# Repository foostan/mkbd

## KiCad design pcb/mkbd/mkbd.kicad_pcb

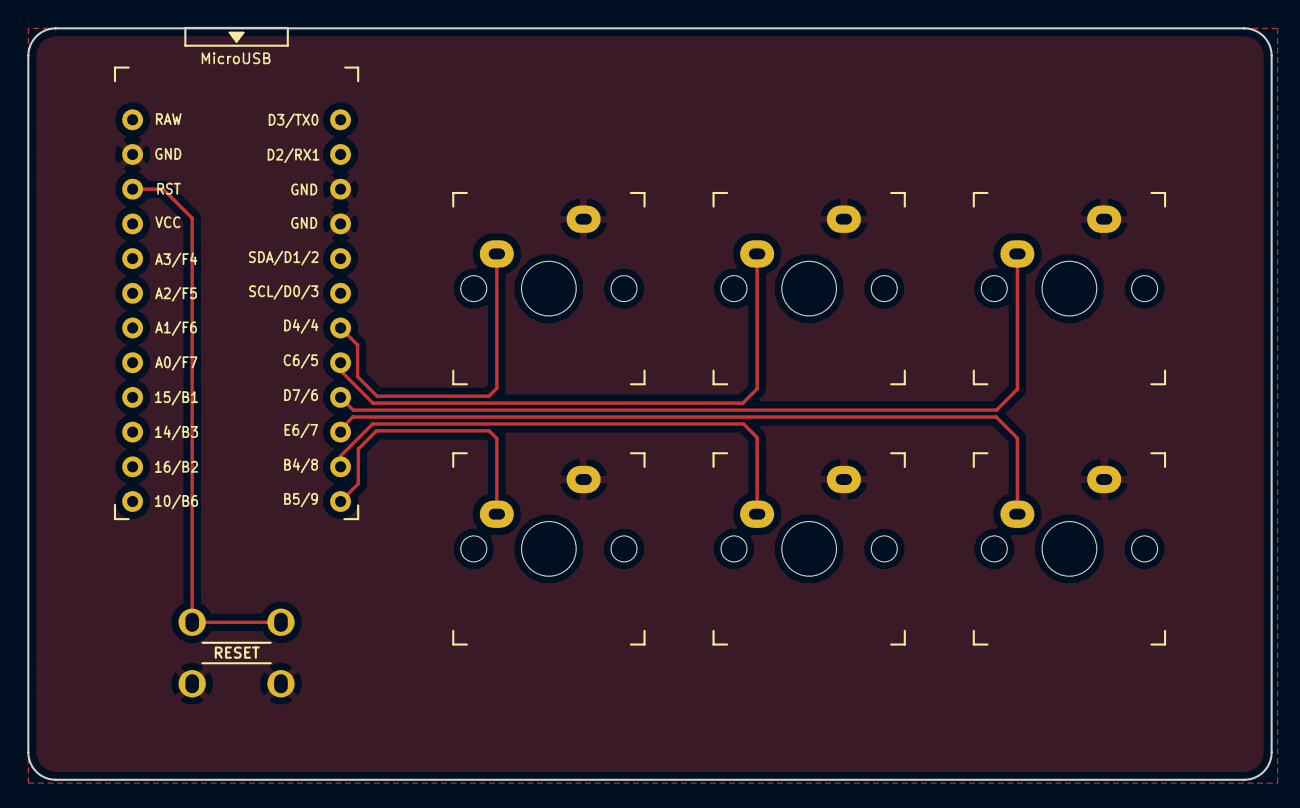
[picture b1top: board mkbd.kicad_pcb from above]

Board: 2 copper layers, 91.0 x 55.0 mm, 8 parts (0 on the bottom side), 8 nets.

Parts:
RSW1: SW_Push; ResetSW_4
SW1, SW2, SW3, SW4, SW5, SW6: SW_PUSH; CherryMX_1u
U1: ProMicro_r; ProMicro_v3

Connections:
/RESET: RSW1.1, U1.22
/SW_1: SW1.1, U1.7
/SW_2: SW2.1, U1.8
/SW_3: SW3.1, U1.9
/SW_4: SW4.1, U1.10
/SW_5: SW5.1, U1.11
/SW_6: SW6.1, U1.12
GND: RSW1.2, SW1.2, SW2.2, SW3.2, SW4.2, SW5.2, SW6.2, U1.3, U1.4, U1.23

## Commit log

2019-04-20 Add meishi pcb
2019-04-20 Add developers_guide
2019-05-08 Fix Decimal point position
    @foostan
    I think this grid settings is wrong.
    I've fixed it.
    `1.905` -> `19.05`
    thx
2020-06-02 Fix clashed
2021-05-16 Renamed file
